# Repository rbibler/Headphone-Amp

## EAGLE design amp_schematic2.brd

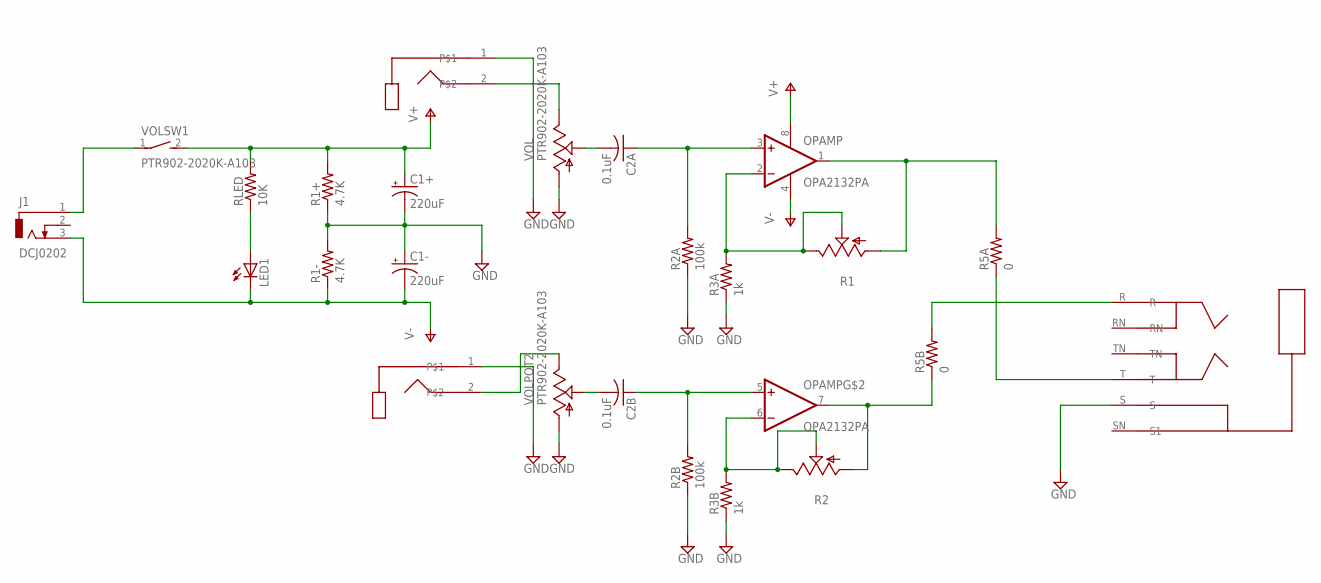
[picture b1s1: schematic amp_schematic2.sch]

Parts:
C1+, C1-: 220uF; E3,5-8
C2A, C2B: 0.1uF; C050-025X075
J1: DCJ0202
LED1: LED5MM
LEFT: RCAJACK
OPAMP: OPA2132PA; DIP254P762X508-8
OUTPUT: STEROJACK; STEREOJACK
R1, R2: TRIM_US-B25U; B25U
R1+, R1-: 4.7K; 0204V
R2A, R2B: 100k; 0204V
R3A, R3B: 1k; 0204V
R5A, R5B: 0; 0204V
RIGHT: RCAJACK
RLED: 10K; 0204V
VOL: PTR902-2020K-A103; PTR902

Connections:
GND: C1+.-, C1-.+, LEFT.1, OUTPUT.S, R1+.1, R1-.2, R2A.1, R2B.1, R3A.1, R3B.1, RIGHT.1, VOL.1A (A), VOL.1B (A)
unnamed: LED1.A, RLED.1
unnamed: C2A.2, VOL.2A (S)
unnamed: C2B.1, OPAMP.5 (+INB), R2B.2
unnamed: C2A.1, OPAMP.3 (+INA), R2A.2
unnamed: OPAMP.2 (-INA), R1.E, R1.S, R3A.2
unnamed: C2B.2, VOL.2B (S)
unnamed: OPAMP.6 (-INB), R2.E, R2.S, R3B.2
unnamed: LEFT.2, VOL.3A (E)
unnamed: OUTPUT.R, R5B.2
unnamed: OUTPUT.T, R5A.1
unnamed: RIGHT.2, VOL.3B (E)
unnamed: OPAMP.7 (OUTB), R2.A, R5B.1
unnamed: OPAMP.1 (OUTA), R1.A, R5A.2
SW1: J1.1, VOL.1
V+: C1+.+, OPAMP.8 (V+), R1+.2, RLED.2, VOL.2 (S)
V-: C1-.-, J1.3, LED1.K (C), OPAMP.4 (V-), R1-.1

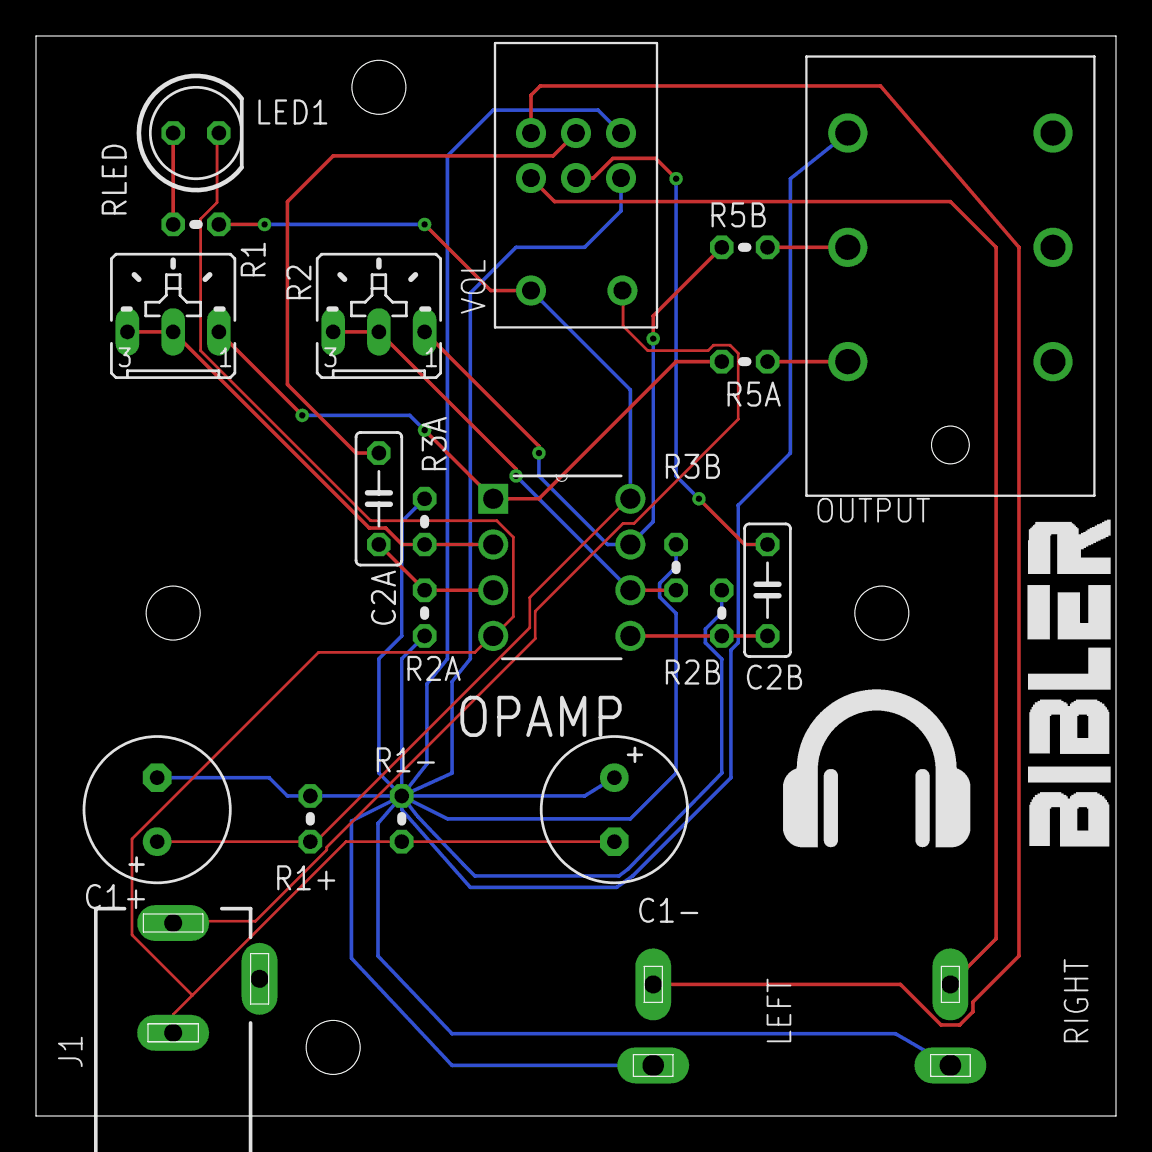
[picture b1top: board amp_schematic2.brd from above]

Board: 2 copper layers, 60.0 x 60.0 mm, 22 parts (0 on the bottom side), 17 nets.

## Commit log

2019-05-21 :space_invader: Added .gitattributes & .gitignore files
2019-05-21 made some changes
    yo diggity
2019-05-22 Finalized layout
    Need to double check that part dimensions are correct.
2019-05-22 Added the bibler logo
